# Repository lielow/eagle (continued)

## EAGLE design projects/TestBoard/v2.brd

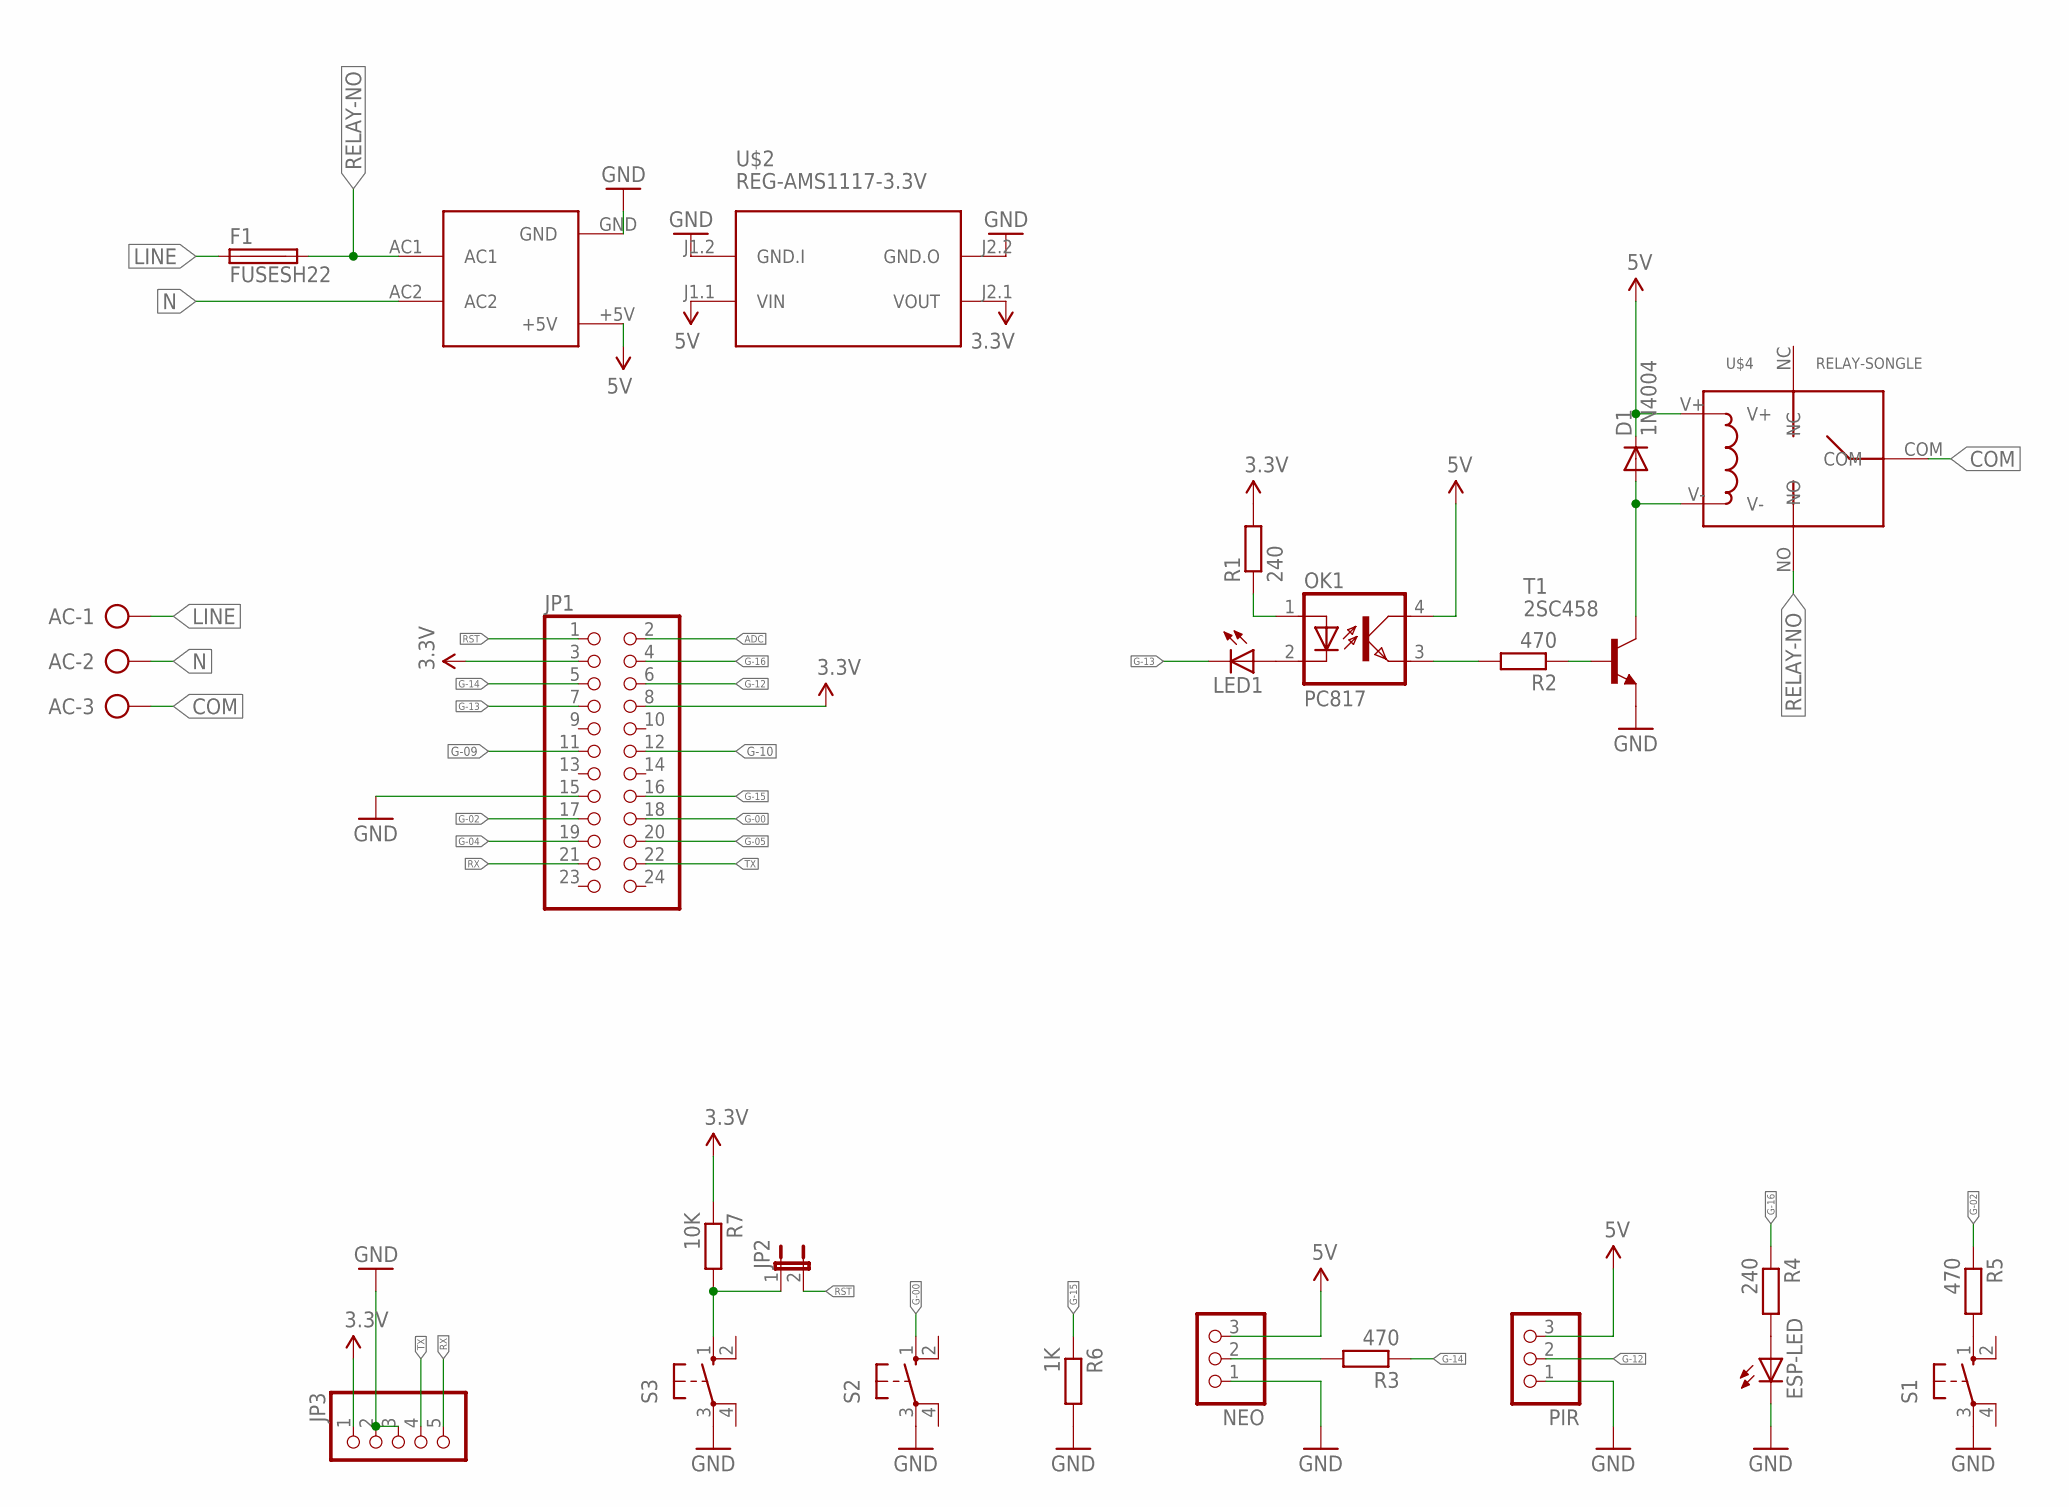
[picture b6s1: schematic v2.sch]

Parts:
AC: AK300/3
D1: 1N4004; DO41-10
ESP-LED: LED5MM
F1: FUSESH22; SH22
JP1: PINHD-2X12; 2X12
JP2: JUMPER-2PTH; 1X02
JP3: PINHD-1X5; 1X05
LED1: LED5MM
NEO: PINHD-1X3; 1X03
OK1: PC817; DIL04
PIR: PINHD-1X3; 1X03
R1, R4: 240; 0204/5
R2, R3, R5: 470; 0204/5
R6: 1K; 0204/5
R7: 10K; 0204/5
S1, S2, S3: 10-XX; B3F-10XX
T1: 2SC458; TO92-ECB
U$1: HLK-PM01
U$2: REG-AMS1117-3.3V; REG-AMS1117
U$4: RELAY-SONGLE

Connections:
3.3V: JP1.3, JP1.8, JP3.1, R1.2, R7.1, U$2.J2.1 (VOUT)
5V: D1.C, NEO.3, OK1.4 (COL), PIR.3, U$1.+5V, U$2.J1.1 (VIN), U$4.V+
ADC: JP1.2
COM: AC.3, U$4.COM
G-00: JP1.18, S2.1 (S)
G-02: JP1.17, R5.1
G-04: JP1.19
G-05: JP1.20
G-09: JP1.11
G-10: JP1.12
G-12: JP1.6, PIR.2
G-13: JP1.7, LED1.K (C)
G-14: JP1.5, R3.1
G-15: JP1.16, R6.1
G-16: JP1.4, R4.1
GND: ESP-LED.K (C), JP1.15, JP3.2, JP3.3, NEO.1, PIR.1, R6.2, S1.3, S2.3, S3.3, T1.E, U$1.GND, U$2.J1.2 (GND.I), U$2.J2.2 (GND.O)
LINE: AC.1, F1.1
N: AC.2, U$1.AC2
unnamed: LED1.A, OK1.2 (C)
unnamed: OK1.1 (A), R1.1
unnamed: OK1.3 (EMIT), R2.2
unnamed: R2.1, T1.B
unnamed: D1.A, T1.C, U$4.V-
unnamed: NEO.2, R3.2
unnamed: R5.2, S1.1 (S)
unnamed: ESP-LED.A, R4.2
unnamed: JP2.1, R7.2, S3.1 (S)
RELAY-NO: F1.2, U$1.AC1, U$4.NO
RST: JP1.1, JP2.2
RX: JP1.21, JP3.5
TX: JP1.22, JP3.4

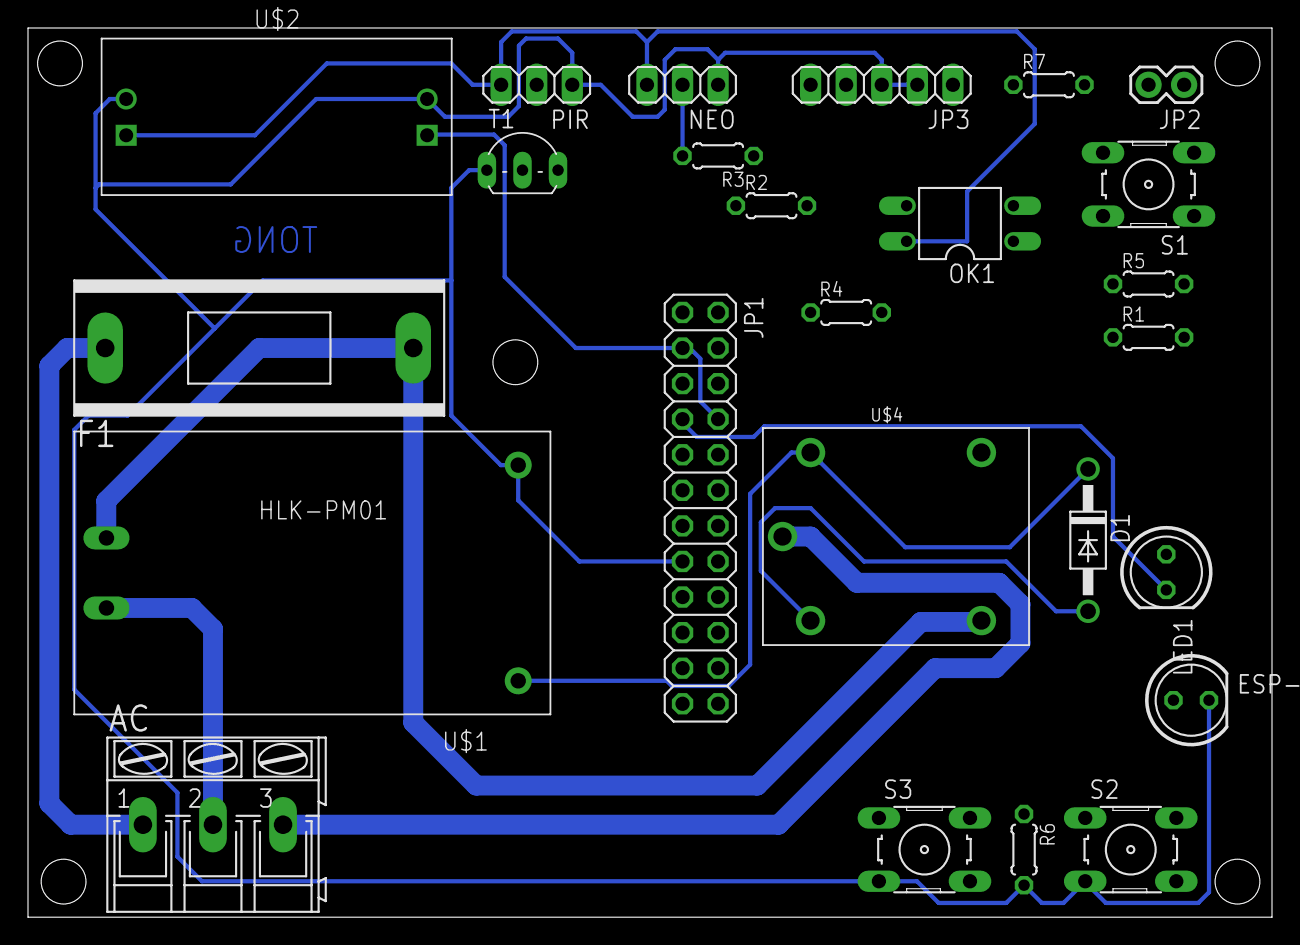
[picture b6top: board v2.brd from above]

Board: 2 copper layers, 88.8 x 63.5 mm, 25 parts (0 on the bottom side), 26 nets.

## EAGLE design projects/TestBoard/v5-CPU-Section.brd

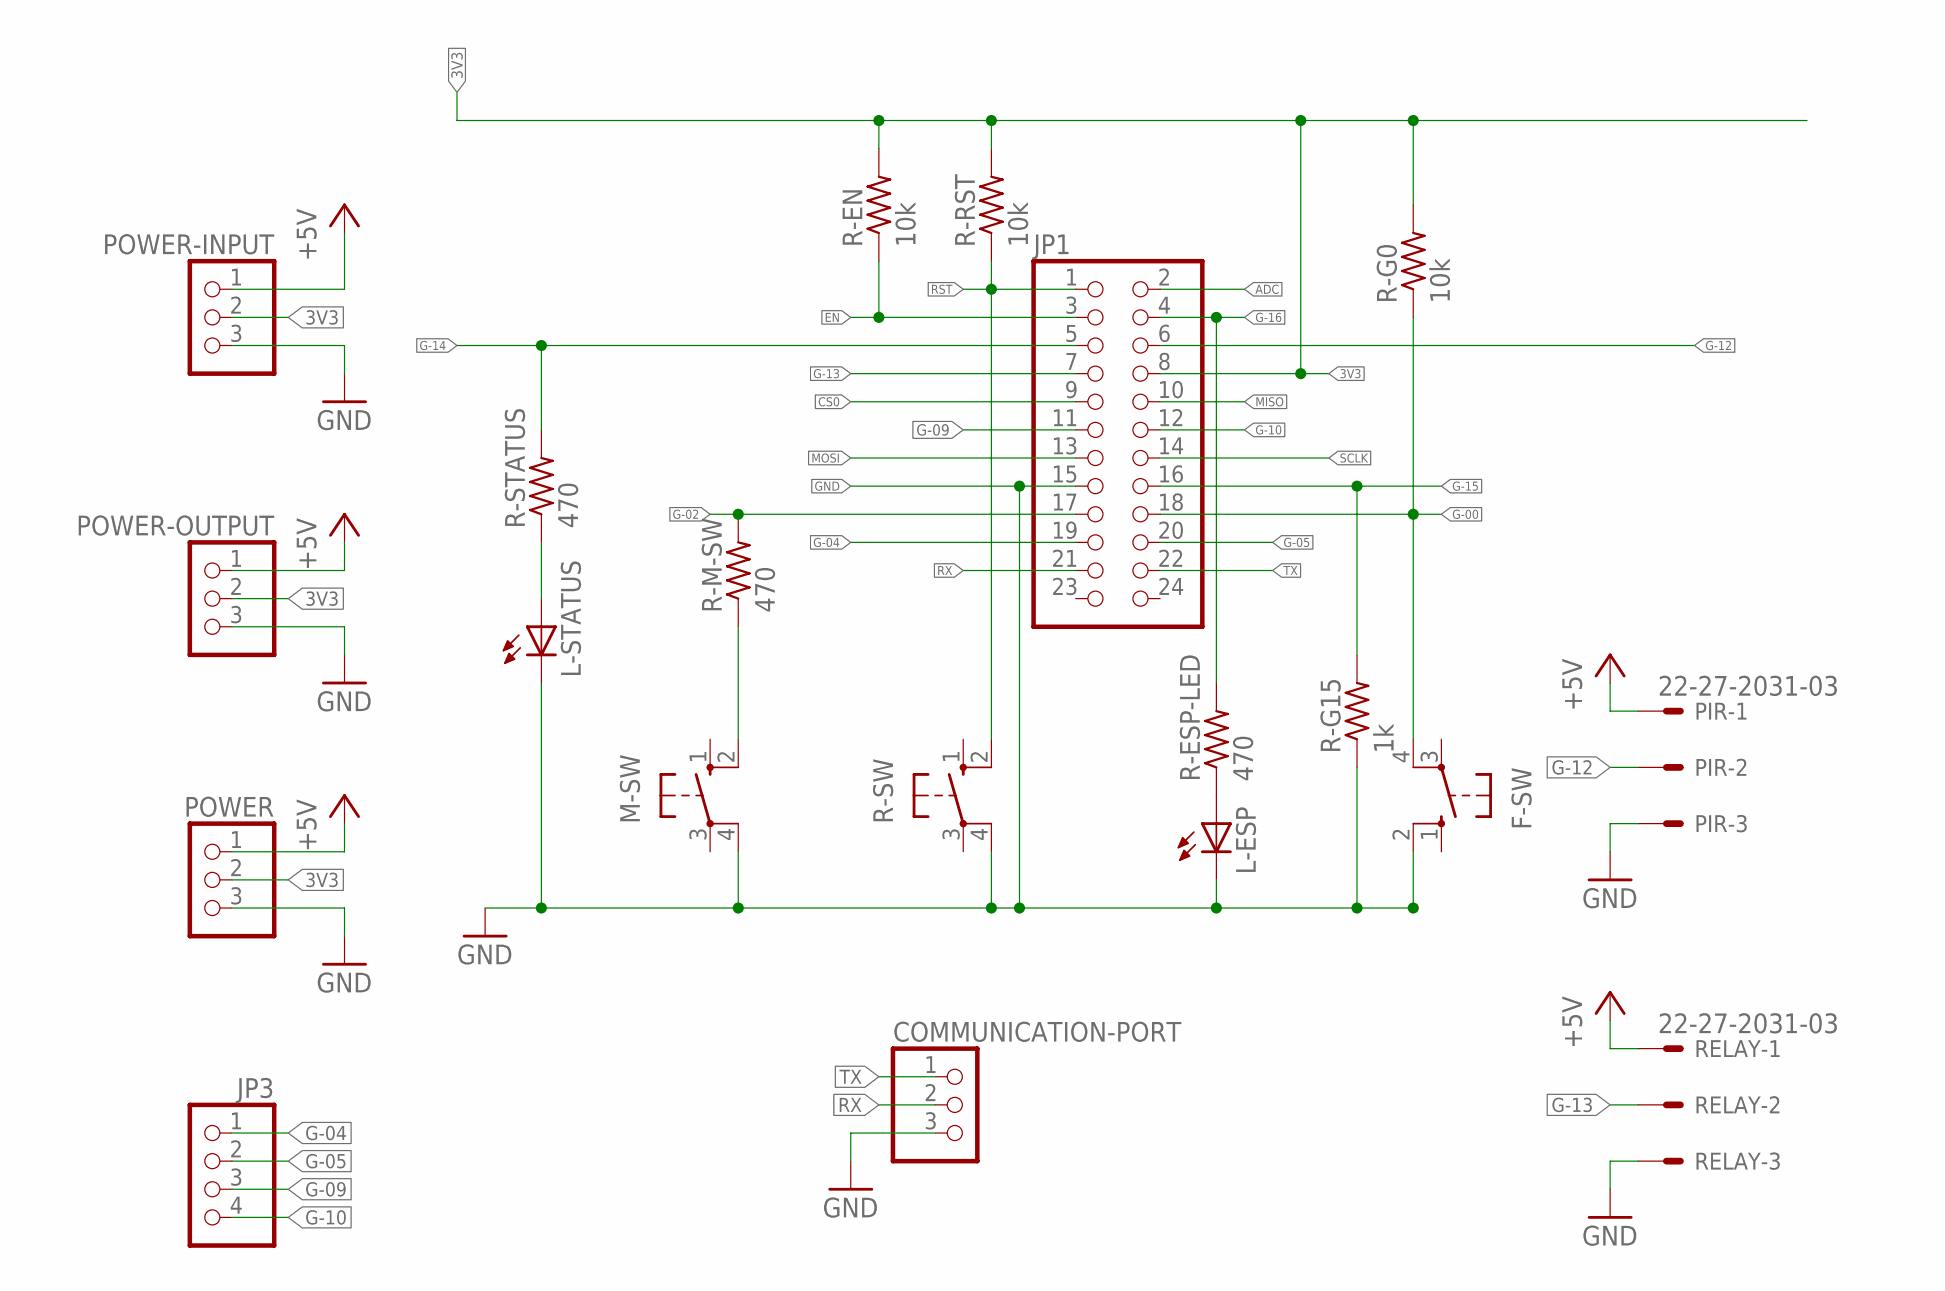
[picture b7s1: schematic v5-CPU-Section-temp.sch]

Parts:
COMMUNICATION-PORT: PINHD-1X3; 1X03
F-SW: 10-XX; B3F-10XX
JP1: PINHD-2X12; 2X12
JP3: PINHD-1X4; 1X04
L-ESP: LED3MM
L-STATUS: LED3MM
M-SW: 10-XX; B3F-10XX
PIR: 22-27-2031-03; 6410-03
POWER: PINHD-1X3; 1X03
POWER-INPUT: PINHD-1X3; 1X03
POWER-OUTPUT: PINHD-1X3; 1X03
R-EN: 10k; 0207/7
R-ESP-LED: 470; 0207/7
R-G0: 10k; 0207/7
R-G15: 1k; 0207/7
R-M-SW: 470; 0207/7
R-RST: 10k; 0207/7
R-STATUS: 470; 0207/7
R-SW: 10-XX; B3F-10XX
RELAY: 22-27-2031-03; 6410-03

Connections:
3V3: JP1.8, POWER.2, POWER-INPUT.2, POWER-OUTPUT.2, R-EN.2, R-G0.2, R-RST.2
+5V: PIR.1, POWER.1, POWER-INPUT.1, POWER-OUTPUT.1, RELAY.1
ADC: JP1.2
CS0: JP1.9
EN: JP1.3, R-EN.1
G-00: F-SW.4 (P1), JP1.18, R-G0.1
G-02: JP1.17, R-M-SW.2
G-04: JP1.19, JP3.1
G-05: JP1.20, JP3.2
G-09: JP1.11, JP3.3
G-10: JP1.12, JP3.4
G-12: JP1.6, PIR.2
G-13: JP1.7, RELAY.2
G-14: JP1.5, R-STATUS.2
G-15: JP1.16, R-G15.2
G-16: JP1.4, R-ESP-LED.2
GND: COMMUNICATION-PORT.3, F-SW.2 (S1), JP1.15, L-ESP.K (C), L-STATUS.K (C), M-SW.4 (P1), PIR.3, POWER.3, POWER-INPUT.3, POWER-OUTPUT.3, R-G15.1, R-SW.4 (P1), RELAY.3
MISO: JP1.10
MOSI: JP1.13
unnamed: L-STATUS.A, R-STATUS.1
unnamed: L-ESP.A, R-ESP-LED.1
unnamed: M-SW.2 (S1), R-M-SW.1
RST: JP1.1, R-RST.1, R-SW.2 (S1)
RX: COMMUNICATION-PORT.2, JP1.21
SCLK: JP1.14
TX: COMMUNICATION-PORT.1, JP1.22

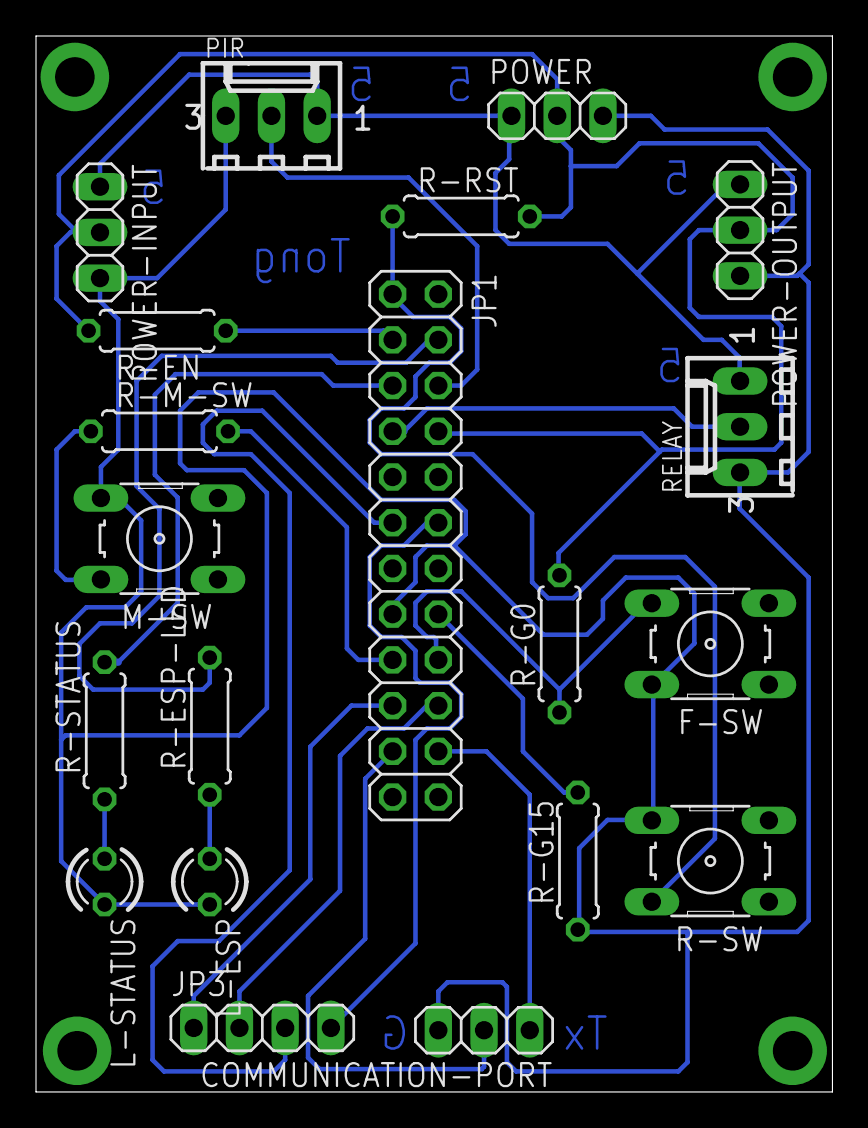
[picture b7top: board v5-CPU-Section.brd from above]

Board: 2 copper layers, 44.2 x 58.7 mm, 20 parts (0 on the bottom side), 21 nets.
